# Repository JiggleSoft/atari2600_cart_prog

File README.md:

# JiggleSoft
---
## atari2600_cart_prog
Atari 2600 Budget Cartridges and Budget Programmer. 

Home on GitHub (https://github.com/JiggleSoft/atari2600_cart_prog)
---
### Project Status
 * This project is in the initial design stage to allow for testing.
---
### Project Contents Summary
 * Atari 2600 Budget ROM Cartridge.
   * Target of < $3.00 cost each (PCB and components, excluding shell).
   * 4K ROM, manually switchable from 128KB, 256KB, or 512KB (depending on chip installed).
 * Atari 2600 Budget ROM/RAM/Bank Switching Cartridge.
   * Target of < $6.00 cost each (PCB and components, excluding shell).
   * ROM of 128KB, 256KB, or 512KB (depending on chip installed).
   * RAM of 128KB (optional installation).
   * PLD providing various Bank Switching methods e.g. 8K, 16K, 32K, up to 512KB ROM + RAM options.
   * DPC functionality if resources allow. 
   * Multi-cart boot menu (optional and depends on images installed).
 * Atari 2600 Budget Programmer.
   * Target of < $15.00 cost each (PCB and components).
   * USB CDC Serial Port connection to PC.
   * Budget Cartridges (both of those above) can be plugged in directly for programming Atari 2600 ROM images.
   * Budget Cartridges (both of those above) can be plugged in directly for dumping the Atari 2600 ROM images.
   * Nice to have (if possible):-
     * Allow dumping other Atari 2600 cartridge ROMs.
     * Allow dumping Atari 7800 cartridge ROMs.
     * Allow dumping other platform ROMs.
	 * Allow programming other platforms cartridges.
 * Note:
   * The PLD will likely require a separate programmer to flash it.
---
### Contact
 * Justin Lane (atari2600@jigglesoft.co.uk)
---
### Repository Contents
 * doc/ --- Documentation
 * eng/ --- Shared engineering files.
 * rom_cart/ - Budget ROM cartridge (WIP).
 * cart_programmer/ -- Cartridge Programmer related files (WIP).
 * rom_ram_pld_cart/ - Budget ROM/RAM/Bank Switching cartridge (WIP).
 * internal_rom/ -- Investigation into the Atari 2600 internal ROM that was never used (incomplete).
---
### Pictures

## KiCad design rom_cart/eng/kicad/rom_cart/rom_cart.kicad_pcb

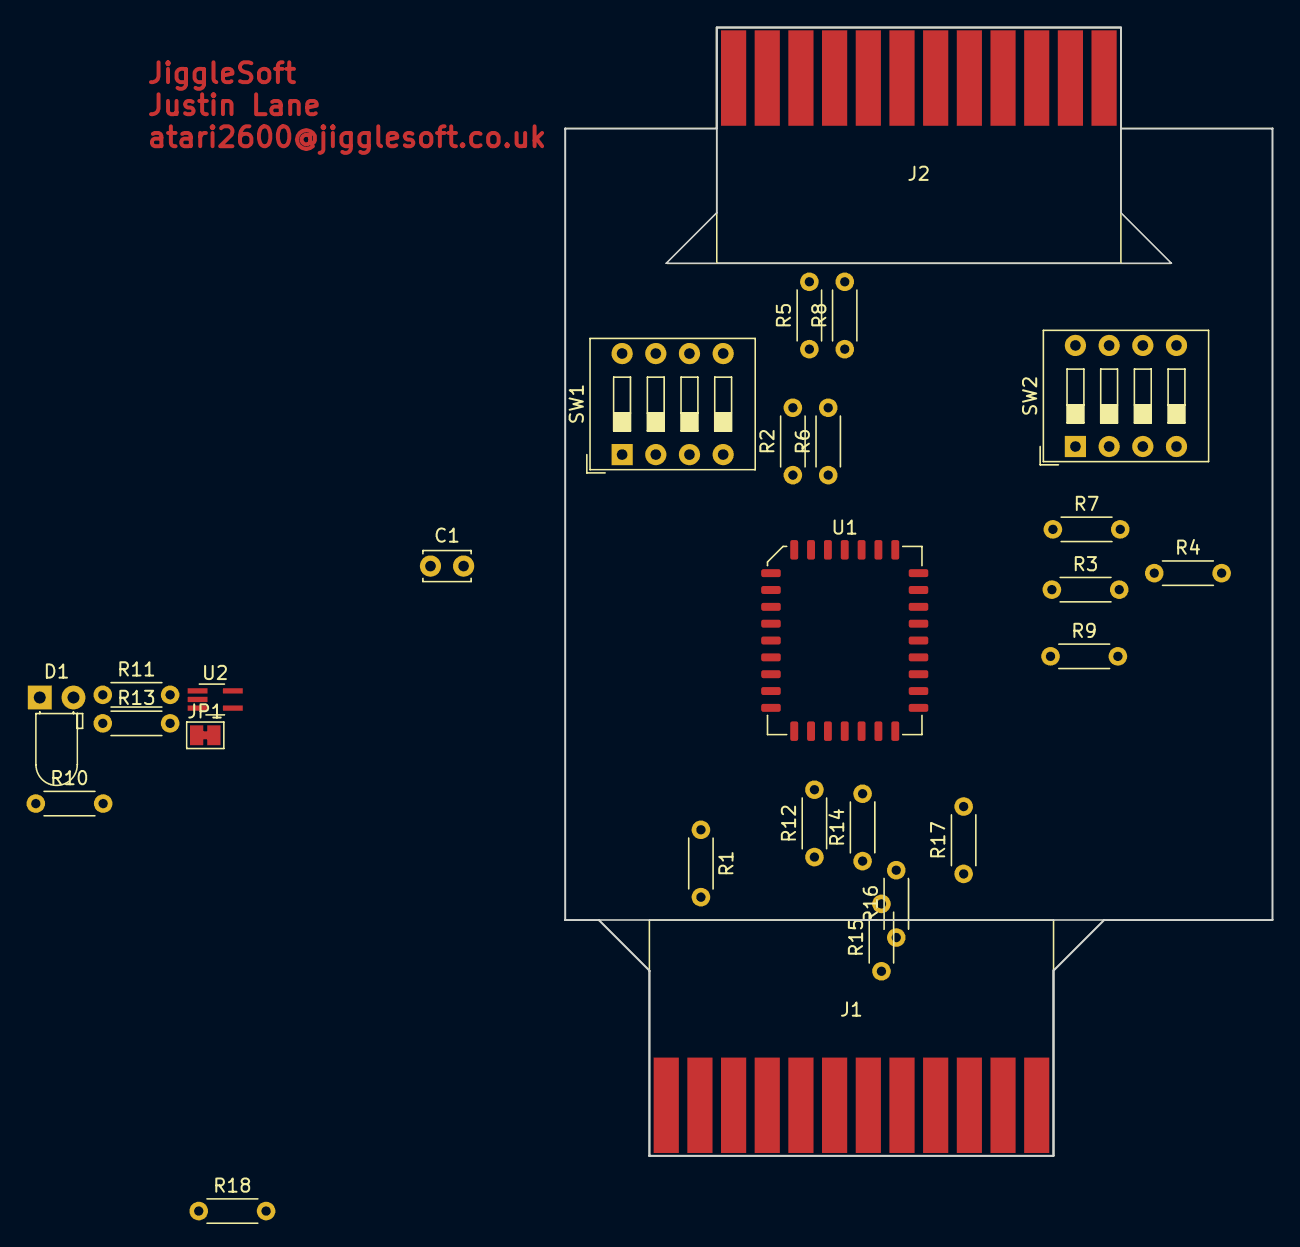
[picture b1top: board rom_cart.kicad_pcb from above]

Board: 2 copper layers, 53.3 x 85.1 mm, 27 parts (0 on the bottom side), 35 nets, no tracks yet.

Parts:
C1: 0.1uF; C_Disc_D3.4mm_W2.1mm_P2.50mm
D1: LED; LED_D3.0mm_Horizontal_O1.27mm_Z2.0mm_Clear
J1: CONN_A2K6_CART_CARD; Atari_2600_Cartridge_2x12_PCB_Edge
J2: CONN_512K_CART_CARD; Atari_2600_Cartridge_2x12_PCB_Edge
JP1: Jumper_NC_Small; SolderJumper-2_P1.3mm_Bridged_Pad1.0x1.5mm
R1, R2, R3, R4, R5, R6, R7, R8, R9: 10K; R_Axial_DIN0204_L3.6mm_D1.6mm_P5.08mm_Horizontal
R10, R11, R12, R13, R14, R15, R16, R17: 470R; R_Axial_DIN0204_L3.6mm_D1.6mm_P5.08mm_Horizontal
R18: R; R_Axial_DIN0204_L3.6mm_D1.6mm_P5.08mm_Horizontal
SW1, SW2: SW_DIP_x04; SW_DIP_SPSTx04_Slide_9.78x12.34mm_W7.62mm_P2.54mm
U1: SST39SF040-70-4C-NHE; PLCC-32_11.4x14.0mm_P1.27mm
U2: 74HCT1G04; SOT-353_SC-70-5_Handsoldering

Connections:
+5V: C1.1, J1.23, J2.12, JP1.1, R1.2, SW1.1, SW1.2, SW1.3, SW1.4, SW2.1, SW2.2, SW2.3, SW2.4, U1.32, U2.5
/A0: J1.8, U1.12
/A1: J1.7, U1.11
/A2: J1.6, U1.10
/A3: J1.5, U1.9
/A4: J1.4, J2.24, U1.8
/A5: J1.3, J2.22, U1.7
/A6: J1.2, J2.21, U1.6
/A7: J1.1, J2.20, U1.5
/A8: J1.22, J2.7, U1.27
/A9: J1.21, J2.6, U1.26
/A10: J1.19, J2.3, U1.23
/A11: J1.20, J2.5, U1.25
/A12: J2.17, R2.1, SW1.8, U1.4
/A13: J2.8, R3.1, SW1.7, U1.28
/A14: J2.9, R4.1, SW1.6, U1.29
/A15: J2.16, R5.1, SW1.5, U1.3
/A16: J2.15, R6.1, SW2.8, U1.2
/A17: J2.10, R7.1, SW2.7, U1.30
/A18: J2.13, R8.1, SW2.6, U1.1
/CE: J1.18, J2.2, U2.2
/D0: J1.9, R10.2, U1.13
/D1: J1.10, R11.2, U1.14
/D2: J1.11, R12.2, U1.15
/D3: J1.13, R13.2, U1.17
/D4: J1.14, R14.2, U1.18
/D5: J1.15, R15.2, U1.19
/D6: J1.16, R16.2, U1.20
/D7: J1.17, J2.1, R17.2, U1.21
/~CE: U1.22, U2.4
/~OE: J2.4, R9.1, U1.24
/~WE: J2.11, R1.1, U1.31
GND: C1.2, D1.1, J1.12, J1.24, J2.19, R2.2, R3.2, R4.2, R5.2, R6.2, R7.2, R8.2, R9.2, U1.16, U2.3
unnamed: D1.2, R18.2
unnamed: JP1.2, R18.1, SW2.5

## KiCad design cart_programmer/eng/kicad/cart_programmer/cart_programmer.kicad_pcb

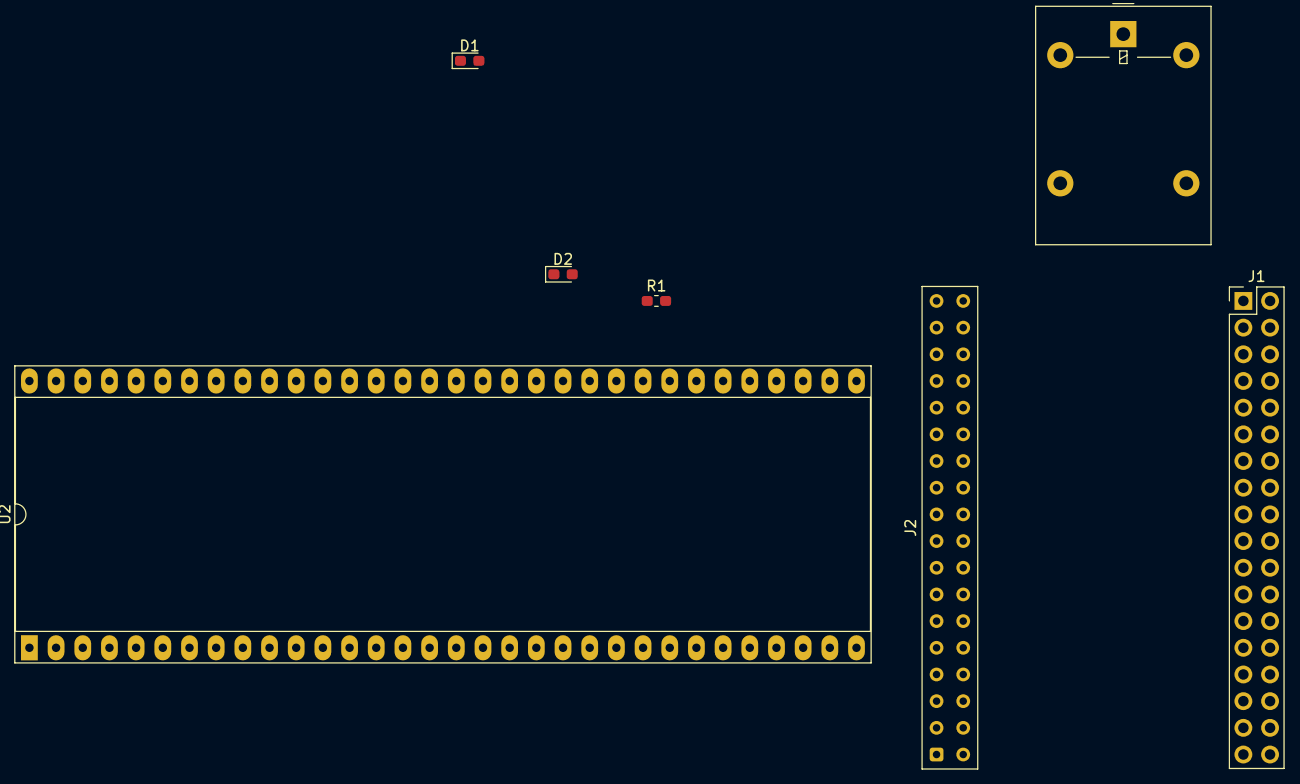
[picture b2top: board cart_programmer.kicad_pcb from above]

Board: 2 copper layers, 7 parts (0 on the bottom side), 2 nets, no tracks yet.

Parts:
D1: D; D_0603_1608Metric_Pad1.05x0.95mm_HandSolder
D2: LED; LED_0603_1608Metric_Pad1.05x0.95mm_HandSolder
J1: CONN_512K_CART_SOCKET_PHY; PinHeader_2x18_P2.54mm_Vertical
J2: CONN_A7K8_CART_CARD_PHY; Samtec_HLE-118-02-xx-DV-TE_2x18_P2.54mm_Horizontal
K1: G5LE-1; Relay_SPDT_Omron-G5LE-1
R1: R; R_0603_1608Metric_Pad1.05x0.95mm_HandSolder
U2: SFH617A-2; DIP-64_W25.4mm_Socket_LongPads

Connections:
/A0: J2.7, J2.9, J2.11
/A1: J2.8, J2.10

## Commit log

2019-01-29 Initial commit of .gitignore and README.md.
2019-01-30 Budget 2K/4K cartridge schematic WIP. Added KiCad libraries for 74xGxx and Microchip Parallel Flash memory. Updated .gitignore for KiCad files.
2019-02-03 Checked in for backup:- Budget ROM Cartridge schematic WIP. Budget Cartridge Programmer schematic WIP. Atari connector schematic symbols. Microchip Curiosity board schematic symbols.
2019-02-05 Checked in for backup: schematics and PCBs.
2019-02-07 Checked in for backup:- * Cartridge schematic and PCB WIP. * Programmer schematic WIP.
2019-02-10 Checked in for backup:- * Cartridge schematic WIP. * Connectors PCB socket and card. * PCB Connector layout WIP.
2019-02-10 Updated the README.md file with latest status.
2019-02-10 Cartridge schematic nearing completion.
2019-02-10 Latest development branch integrated into master branch. Budget cartridge schematic nearing completion. Cartridge PCB and programmer schematic and PCB early days.
2019-02-11 Atari 2600 Budget ROM Cartridge candidate schematic.
2019-02-11 Atari 2600 Budget Flash ROM Cartridge PCB layout Work-In-Progress.
2019-02-13 Added Cartridge Programmer Serial Protocol Doc (WIP). Cartridge Programmer schematic (WIP). ROM/RAM/PLD Cartridge project skeleton.
2019-02-13 New symbol libray for Microchip(Atmel) CPLD. ROM/RAM/Bank Switching cartridge schematic (WIP). Updated README.md file.
2019-02-20 Shared KiCAD libraries and modules migrated from atari2600_cart_prog repository develop branch to jigglesoft_kicad_library repository to be validated and sorted out.
2019-02-22 Added LICENCE.txt file to clarify licence in use. Updated ROM cartridge schematic licence information. Updated ROM cartridge schematic with current limiting resistor array to data bus. Added initial 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
2019-02-23 Updated licence for cart_programmer schematic. Updated licence for rom_ram_pld_cart schematic. Updated component references from both of those schematics. Latest cartridge programmer serial protocol 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
2019-02-24 Updated .gitignore file (may need to remove .net files from repo). Cartridge programmer schematic WIP.
2019-02-24 Added some pictures to README.md.
2019-02-24 Merge latest 'develop' branch into 'master' branch. (#1)
    * Atari 2600 Budget Flash ROM Cartridge PCB layout Work-In-Progress.
    * Added Cartridge Programmer Serial Protocol Doc (WIP).
    Cartridge Programmer schematic (WIP).
    ROM/RAM/PLD Cartridge project skeleton.
    * New symbol libray for Microchip(Atmel) CPLD.
    ROM/RAM/Bank Switching cartridge schematic (WIP).
2019-02-27 Latest cartridge programmer schematic. Checked in for backup. Going to move to thru-hole components for ease of build at expense of size. Also having problems obtaining SMD devices and I have buckets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
2019-03-23 Changed to through-hole caps and resistors. May back out.
2019-03-23 Latest cart programmer schematic (WIP). Checked in for backup.
2019-03-23 Latest cartridge programmer serial protocol (WIP). Checked in for backup.
